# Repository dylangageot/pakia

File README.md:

# PS/2 to Amiga Keyboard Interface Adapter (PAKIA)

Standalone Amiga keyboards are more than ever difficult to find, especially due to the increased perceived value of Amiga computers and peripherals on the second-hand market.

Unfortunately, the keyboard interface used by Commodore is proprietary, see the [Amiga keyboard interface documentation](http://amigadev.elowar.com/read/ADCD_2.1/Hardware_Manual_guide/node0172.html).
Even though it uses the same 5-pin DIN 41524 connector as IBM AT keyboards, the keyboard interface is still different and therefore not compatible with any easy-to-find PC-compatible keyboards.

PAKIA is yet another adapter circuit, taking a PS/2 keyboard interface in input, and translating it into the Amiga keyboard interface in output.

## Features

- Convert PS/2 scancode to Amiga scancode,
- Handle lost synchronization and corresponding recovery,
- Handle the reset combo (Ctrl + Left Amiga + Right Amiga) with the two reset warnings,
- Interact with PS/2 keyboard to set Caps Lock LED,
- Use the [Menu](https://en.wikipedia.org/wiki/Menu_key) modifier key to type a key that has been absorbed by a larger key on the PS/2 keyboard but is present on an Amiga keyboard,
- PCB with: 
    - on-board DIN socket for AT and PS/2 keyboards connection, with the later usable with a mini-DIN to DIN adapter cable,
    - strain relief for wire coming from the Amiga. 

## Under the hood

Despite being different, both PS/2 and Amiga keyboard interfaces share similarities: they use the same KDAT and KCLK signal pair.
In either case, the keyboard is responsible for generating the clock and preparing 8 data bits to be read on the KDAT signal a falling or rising edge of the KCLK signal.

Leveraging multiple timers and interrupt service routines, an ATtiny85 captures frames sent out from an input PS/2 keyboard, interprets them, and then converts them to the Amiga keyboard interface using a look-up table written in Flash memory.

In contrast to other solutions, signal timings for the Amiga keyboard interface are driven by discrete time events instead of being driven by blocking delays.
One hardware timer generates periodic interrupt requests that once the corresponding ISR runs, the signal is taught to evolve its state through a software-based finite state machine, hence changing pins levels for both KDAT and KCLK.

This asynchronous philosophy makes it possible to incorporate this piece of software in a busier system, without introducing blocking delay when Amiga commands are being sent, minus interrupt service routines execution time of course.

You might think that this is overengineering and that other solutions got it right enough by using blocking delays to handle their signal timings, and you are probably right!
The solution I have implemented was way more stimulating for me to develop, so here we are!

The binary currently weighs 3.2KB, in that regard, one could choose to use an ATtiny45 instead of an ATtiny85, it might be enough even in case of additional features coming in future updates.

The project uses C++ mainly to benefit from namespaces.

## Build and deploy

> [!WARNING]
> The build system is only available on Linux.

> **Required:** `avr-gcc` and `avrdude`, respectively 5.4.0 and 6.3-20171130 on my setup.

1. Specify the programmer to use with `avrdude` in the Makefile, with the variable `PROGRAMMER`,
2. Build with `make`,
3. Deploy with `make flash` while your programmer is wired to the ISP connector on the PCB.

## Edit the translation map

The lookup table to convert PS/2 scancode to Amiga ones is hard-coded in `src/translation_map.hh`.
A tool called `translation-map-generator` can be built from the `tools` directory.
By modifying the source code, one can generate other hard-coded LUT from a readable code:

```bash
(cd tools && make)
tools/translation-map-generator > src/translation_map.hh
```

##  Schematic and PCB

The schematic and PCB were drawn in KiCAD. The project is available in the `hardware` directory.

## Other solutions

> "yet another adapter circuit", is there are other adapter circuits?

Yes, there are other adapter circuits! 

I have started this project blindly, without searching if anyone made one before.
Frankly, it was appealing to my eye, so why not!
I have found documentation on both keyboard interfaces and started developing a proof of concept on an Arduino Uno board, based on an ATmega328p.

I have discovered many of them once I had finished the prototype for PAKIA and wanted to design a PCB for it, with eventually a lighter microcontroller than the ATmega328p.
Here is a list of related open-source projects and their respective solutions:

- [AKAB](https://gitlab.com/hkzlab-retrocomputing/AKAB_Reloaded) by [hkzlabnet](http://mercatopo-en.blogspot.com/)
    - uses an ATmega328p as a microcontroller (32KB Flash, 2KB SRAM),
    - leverages a pure AVR development environment,
    - provides a KiCAD project with schematic and PCB design,
    - PCB based on both through-hole DIP-28 ATmega328p and mini-DIN socket,
    - see a photo of the adapter board in [the dedicated blog article](http://mercatopo-en.blogspot.com/2013/11/first-prototype-of-akab-amiga-keyboard.html),
    - implements Amiga Ctrl-Amiga-Amiga reset combo keys, 
- [PS2toAmiga](https://github.com/Jartza/PS2toAmiga) by [Jartza](https://github.com/Jartza)
    - uses an ATtiny85 as a microcontroller (8K Flash, 512B SRAM),
    - leverages the Arduino development environment,
    - provides a KiCAD project with schematic and PCB design,
    - PCB based on SMD SOIC8 ATtiny85 and pads to solder wires on for both PS/2 and Amiga keyboard wires,
    - designed to fit inside a keyboard,
    - see photos of the adapter board on the repository README.md,
    - implements Amiga Ctrl-Amiga-Amiga reset combo keys, 
    - two different keyboard layouts selectable from the *Scroll Lock* key.

There is also the [Lyra 3](http://wiki.icomp.de/wiki/Lyra_3) adapter sold by Individual Computers.
This one is very complete feature-wise, but I did not want to buy one as I thought that it would spoil my pleasure of developing my own, I'm sure you get it, right?

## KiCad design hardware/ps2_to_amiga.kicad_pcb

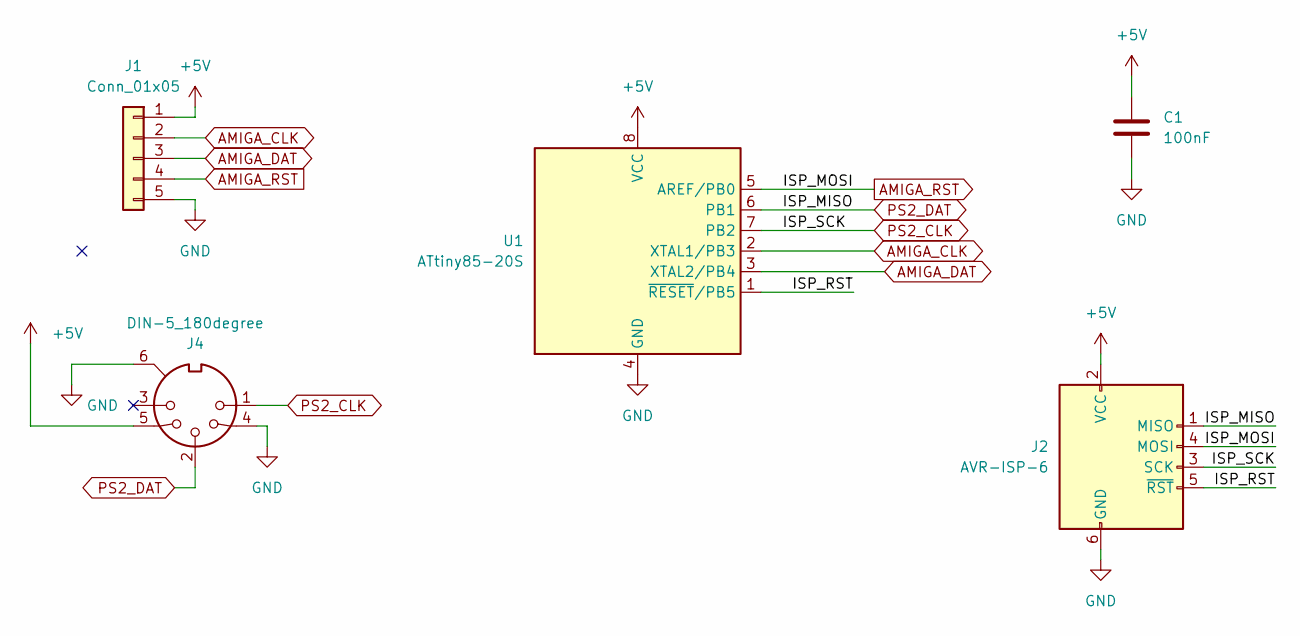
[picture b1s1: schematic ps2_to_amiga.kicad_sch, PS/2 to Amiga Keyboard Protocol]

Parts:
C1: 100nF; C_1206_3216Metric_Pad1.33x1.80mm_HandSolder
J1: Conn_01x05; AMIGA_KB_PADS
J2: AVR-ISP-6; PinHeader_2x03_P2.54mm_Vertical
J4: DIN-5_180degree; DIN_5PIN_180d_Female
U1: ATtiny85-20S; SOIC-8W_5.3x5.3mm_P1.27mm

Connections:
+5V: C1.1, J1.1, J2.2 (VCC), J4.5, U1.8 (VCC)
/ISP_RST: J2.5 (~RST), U1.1 (~RESET/PB5)
AMIGA_CLK: J1.2, U1.2 (XTAL1/PB3)
AMIGA_DAT: J1.3, U1.3 (XTAL2/PB4)
AMIGA_RST: J1.4, J2.4 (MOSI), U1.5 (AREF/PB0)
GND: C1.2, J1.5, J2.6 (GND), J4.4, J4.6, U1.4 (GND)
PS2_CLK: J2.3 (SCK), J4.1, U1.7 (PB2)
PS2_DAT: J2.1 (MISO), J4.2, U1.6 (PB1)

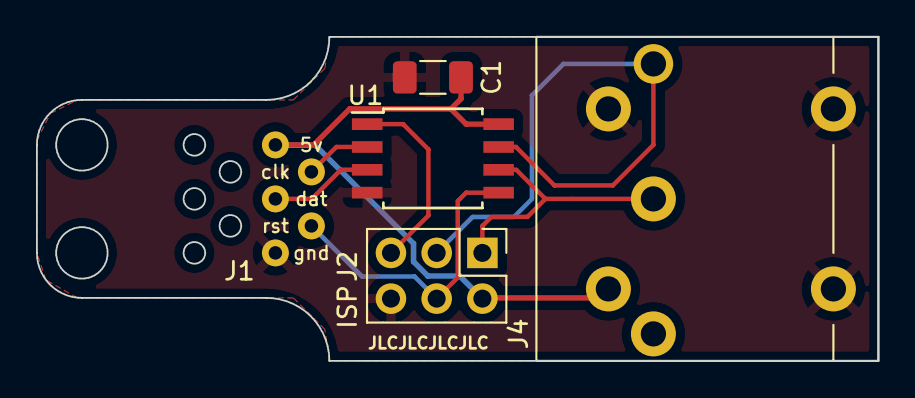
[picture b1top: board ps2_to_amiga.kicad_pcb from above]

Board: 2 copper layers, 46.8 x 18.0 mm, 5 parts (0 on the bottom side), 8 nets.

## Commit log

2024-02-10 Acquire the buffer value as fast as possible
2024-02-12 Use usual way of handling interrupt
2024-02-12 Swap function pointer for PS/2 interrupt state machine
2024-02-12 Add ps2 module
2024-02-12 Add a rolling buffer for received ps2 key
2024-02-12 Remove useless newline
2024-02-12 Transfer 8bit of data to amiga
2024-02-12 Fix timing
2024-02-18 Use PB0 and PB1 for amiga pins
2024-02-18 Set up interrupt on falling edge to detect acknowledgement
2024-02-18 WIP: wait_for_ack
2024-02-18 Add config for timer for resync
2024-02-18 Handle acknowledgement
2024-02-18 Refactor int0 isr
2024-02-18 Set flag to 0 for int0 before enabling the interruption
2024-02-18 Send key for stream, but it fails to reckons acknowledge now...
2024-02-18 Fix problem with INT0 interrup
2024-02-19 Succeed get sync
2024-02-19 Successfully printed the first character on the amiga
2024-02-19 Add amiga.cpp
2024-02-19 letter key works
2024-02-19 Add function line
2024-02-22 Update the plan
2024-02-22 Take care of Caps Locks and essentials keys
2024-02-22 Introduce concept of frame_iterator
2024-02-22 Remove useless volatile qualifier for ps2_fsm and amiga_fsm
2024-02-23 Change coding style
2024-02-23 Create a circular buffer struct
2024-02-23 Refactor ps2 module
2024-02-23 Refactor amiga and ps2 module
2024-02-23 Rewrite main
2024-02-23 Fix typo in iterator
2024-02-23 Inhibit in case parity or any bit is wrong
2024-02-24 Complete translation map
2024-02-25 Use a single byte to remember which key was pressed
2024-02-25 Add translation map generator tool
2024-02-25 Add Kicad schematic and pcb
2024-03-07 Move Arduino src to src.old
2024-03-07 Add Makefile and gitignore
2024-03-07 Update Makefile to build in a dir
2024-03-07 Refactor repo
2024-03-07 Setup VSCode to use avr-gcc
2024-03-10 Switch to C++
2024-03-10 Add pins.hh
2024-03-11 Add pinout ascii drawing
2024-03-11 Validate INT0 interrupt
2024-03-11 Move all source to same dir
2024-03-11 Put everything together
2024-03-11 Remove old Arduino prototype
2024-03-11 Fix PORTB replacement for input reading with PIN
2024-04-01 Fix many issue with shift+delete, keypad arrangement
2024-04-07 Add README.md
2024-04-07 Fix lines positioning in README.md
2024-04-07 Fix typo
2024-04-07 Change project name, update README.md
2024-04-07 Add GPLv3 license
2024-04-07 Add .vscode to gitignore
2024-04-07 Fix typo in README.md
2024-04-07 Fix missing include in translation map generator
2024-04-08 Add scancodes.hh
2024-04-08 Refactor using scancodes translation map generator
2024-04-08 Reformat whole code base with LLVM style
2024-04-09 Add amiga scancode consts
2024-04-09 Use scancode consts in translation map gen
2024-04-10 Use scancodes in main, rename translation map
2024-04-11 Add DIN-5 180deg angle footprint
2024-04-13 Design rev2 pcb
2024-04-28 Refactor circular buffer
2024-04-28 Fix circular buffer written element
2024-04-28 Use a circular buffer to send data to Amiga
2024-04-28 Remove from headers FSMs
2024-05-09 Handle Ctrl+LAmiga+RAmiga
2024-05-10 Refactor amiga module
2024-05-10 Continue refactoring of amiga module
2024-05-10 Refactor main
2024-05-10 Rename DAT_PIN const to DAT_POS
2024-05-10 Refactor main and amiga module
2024-05-10 Use warning formatting in README.md
2024-05-10 Add PCB photo to README.md
2024-05-10 Resize photo
2024-05-10 Use HTML balise instead of Markdown to display image
2024-05-10 U*pdate README and add individual images
2024-05-10 Change size of photos
2024-05-10 Remove unified photo
2024-05-12 Add prototype function for ps2::send command
2024-05-15 Add support for bidirectional PS/2 com
2024-05-15 Add support for Caps Lock LED
2024-05-15 Refactor main and translation table, using 0xFF as unknown scancode
2024-05-15 Refactor main.cc
2024-05-15 Refactor main and ps2 module
